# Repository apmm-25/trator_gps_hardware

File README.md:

# trator_gps_hardware
# This repository will hold the hardware for the tractor GPS connection board, leveraging an ESP32 microcontroller that will communicate with an ardusimple ZED F9P based board 
  - `board/` (has the ibom.html with the positions and instructions for soldering)
  - `docs/` (has the pdf datasheets of electronics components that were utilized)
  - `default_esp32_board/` (Kicad project with component zips, step model of the board, libraries and manufacture files )

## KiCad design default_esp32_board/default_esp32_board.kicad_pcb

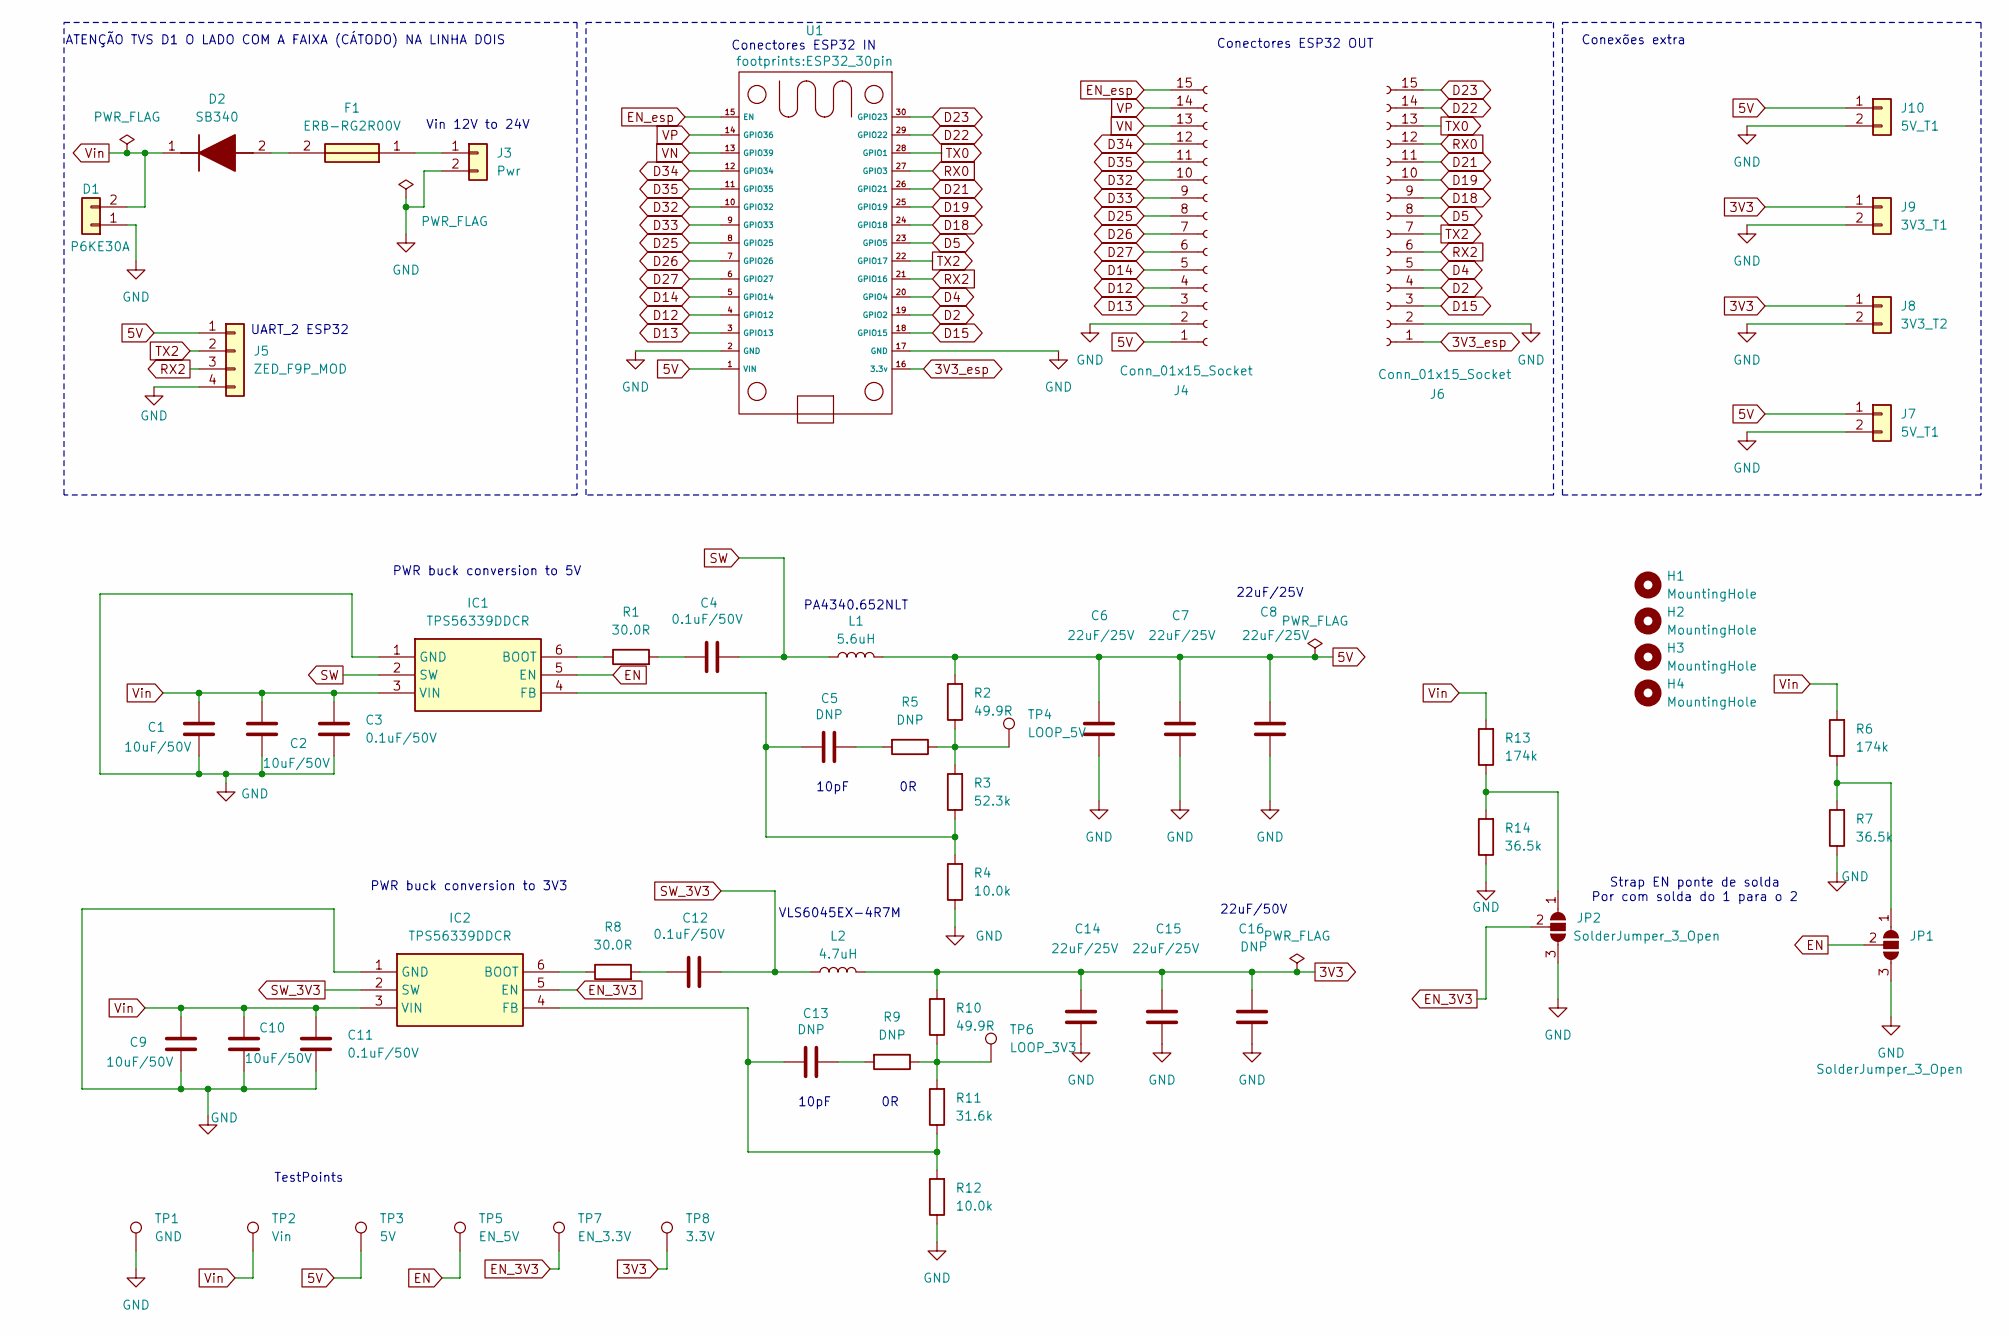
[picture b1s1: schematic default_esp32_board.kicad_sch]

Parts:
C1, C2, C9, C10: 10uF/50V; C_0805_2012Metric_Pad1.18x1.45mm_HandSolder
C3, C4, C11, C12: 0.1uF/50V; C_0805_2012Metric_Pad1.18x1.45mm_HandSolder
C5, C13, C16: DNP; C_0805_2012Metric_Pad1.18x1.45mm_HandSolder
C6, C7, C8, C14, C15: 22uF/25V; C_0805_2012Metric_Pad1.18x1.45mm_HandSolder
D1: P6KE30A; D_DO-15_P5.08mm_Vertical_KathodeUp
D2: SB340; Mouser Part Number 637-SB340
F1: ERB-RG2R00V; ERBRG4R00V; Mouser Part Number 667-ERB-RG2R00V
H1, H2, H3, H4: MountingHole; MountingHole_4.3mm_M4
IC1, IC2: TPS56339DDCR; Mouser Part Number 595-TPS56339DDCR
J3: Pwr; PinHeader_1x02_P2.54mm_Vertical
J4, J6: Conn_01x15_Socket; M20-7821546
J5: ZED_F9P_MOD; PinHeader_1x04_P2.54mm_Vertical
J7, J10: 5V_T1; PinHeader_1x02_P2.54mm_Vertical
J8: 3V3_T2; PinHeader_1x02_P2.54mm_Vertical
J9: 3V3_T1; PinHeader_1x02_P2.54mm_Vertical
JP1, JP2: SolderJumper_3_Open; SolderJumper-3_P1.3mm_Open_Pad1.0x1.5mm_NumberLabels
L1: 5.6uH; PA4340562NLT
L2: 4.7uH; VLS6045
R1, R8: 30.0R; R_0805_2012Metric_Pad1.20x1.40mm_HandSolder
R2, R10: 49.9R; R_0805_2012Metric_Pad1.20x1.40mm_HandSolder
R3: 52.3k; R_0805_2012Metric_Pad1.20x1.40mm_HandSolder
R4, R12: 10.0k; R_0805_2012Metric_Pad1.20x1.40mm_HandSolder
R5, R9: DNP; R_0805_2012Metric_Pad1.20x1.40mm_HandSolder
R6, R13: 174k; R_0805_2012Metric_Pad1.20x1.40mm_HandSolder
R7, R14: 36.5k; R_0805_2012Metric_Pad1.20x1.40mm_HandSolder
R11: 31.6k; R_0805_2012Metric_Pad1.20x1.40mm_HandSolder
TP1: GND; TestPoint_Plated_Hole_D2.0mm
TP2: Vin; TestPoint_Plated_Hole_D2.0mm
TP3: 5V; TestPoint_Plated_Hole_D2.0mm
TP4: LOOP_5V; TestPoint_Plated_Hole_D2.0mm
TP5: EN_5V; TestPoint_Plated_Hole_D2.0mm
TP6: LOOP_3V3; TestPoint_Plated_Hole_D2.0mm
TP7: EN_3.3V; TestPoint_Plated_Hole_D2.0mm
TP8: 3.3V; TestPoint_Plated_Hole_D2.0mm
U1: ESP32_30pin

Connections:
3V3: C14.1, C15.1, C16.1, J8.1, J9.1, L2.2, R10.2, TP8.1
3V3_esp: J6.1, U1.16 (3.3v)
5V: C6.1, C7.1, C8.1, J4.1, J5.1, J7.1, J10.1, L1.2, R2.2, TP3.1, U1.1 (VIN)
D2: J6.4, U1.19 (GPIO2)
D4: J6.5, U1.20 (GPIO4)
D5: J6.8, U1.23 (GPIO5)
D12: J4.4, U1.4 (GPIO12)
D13: J4.3, U1.3 (GPIO13)
D14: J4.5, U1.5 (GPIO14)
D15: J6.3, U1.18 (GPIO15)
D18: J6.9, U1.24 (GPIO18)
D19: J6.10, U1.25 (GPIO19)
D21: J6.11, U1.26 (GPIO21)
D22: J6.14, U1.29 (GPIO22)
D23: J6.15, U1.30 (GPIO23)
D25: J4.8, U1.8 (GPIO25)
D26: J4.7, U1.7 (GPIO26)
D27: J4.6, U1.6 (GPIO27)
D32: J4.10, U1.10 (GPIO32)
D33: J4.9, U1.9 (GPIO33)
D34: J4.12, U1.12 (GPIO34)
D35: J4.11, U1.11 (GPIO35)
EN: IC1.5 (EN), JP1.2 (C), TP5.1
EN_3V3: IC2.5 (EN), JP2.2 (C), TP7.1
EN_esp: J4.15, U1.15 (EN)
GND: C1.2, C2.2, C3.2, C6.2, C7.2, C8.2, C9.2, C10.2, C11.2, C14.2, C15.2, C16.2, D1.1, IC1.1 (GND), IC2.1 (GND), J3.2, J4.2, J5.4, J6.2, J7.2, J8.2, J9.2, J10.2, JP1.3 (B), JP2.3 (B), R4.1, R7.1, R12.1, R14.1, TP1.1, U1.2 (GND), U1.17 (GND)
unnamed: C4.1, R1.2
unnamed: C5.2, R5.2
unnamed: C12.1, R8.2
unnamed: C13.2, R9.2
unnamed: D2.2 (A), F1.2
unnamed: IC1.6 (BOOT), R1.1
unnamed: C5.1, IC1.4 (FB), R3.1, R4.2
unnamed: IC2.6 (BOOT), R8.1
unnamed: C13.1, IC2.4 (FB), R11.1, R12.2
unnamed: F1.1, J3.1
unnamed: JP1.1 (A), R6.1, R7.2
unnamed: JP2.1 (A), R13.1, R14.2
unnamed: R2.1, R3.2, R5.1, TP4.1
unnamed: R9.1, R10.1, R11.2, TP6.1
RX0: J6.12, U1.27 (GPIO3)
RX2: J5.3, J6.6, U1.21 (GPIO16)
SW: C4.2, IC1.2 (SW), L1.1
SW_3V3: C12.2, IC2.2 (SW), L2.1
TX0: J6.13, U1.28 (GPIO1)
TX2: J5.2, J6.7, U1.22 (GPIO17)
VN: J4.13, U1.13 (GPIO39)
VP: J4.14, U1.14 (GPIO36)
Vin: C1.1, C2.1, C3.1, C9.1, C10.1, C11.1, D1.2, D2.1 (K), IC1.3 (VIN), IC2.3 (VIN), R6.2, R13.2, TP2.1

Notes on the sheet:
Vin 12V to 24V
TestPoints
10pF
PA4340.652NLT
Strap EN ponte de solda Por com solda do 1 para o 2
PWR buck conversion to 5V
Conexões extra
PWR buck conversion to 3V3
Conectores ESP32 IN
22uF/50V
UART_2 ESP32
Conectores ESP32 OUT
VLS6045EX-4R7M
ATENÇÃO TVS D1 O LADO COM A FAIXA (CÁTODO) NA LINHA DOIS
22uF/25V

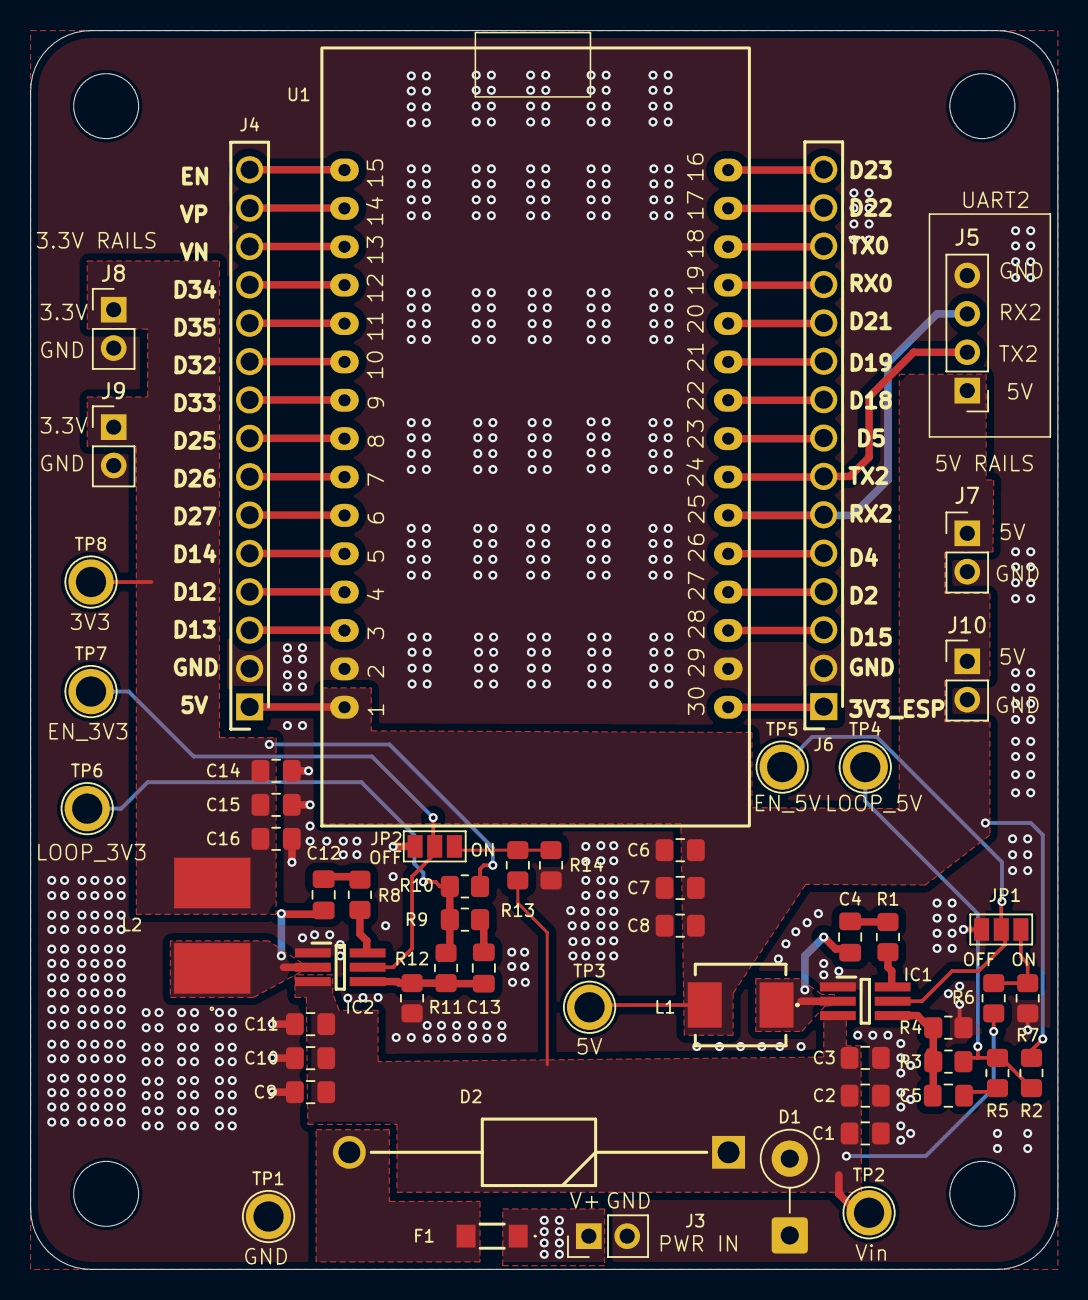
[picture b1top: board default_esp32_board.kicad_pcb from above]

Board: 2 copper layers, 68.0 x 82.0 mm, 60 parts (0 on the bottom side), 49 nets.

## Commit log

2026-06-18 Initial commit with all the current files on the KiCAD hardware development
2026-06-18 Update README with repository structure details
    Added additional details about the repository structure and contents.
2026-06-18 Format README.md for better readability
2026-06-19 Fixed esp32 30 pin footprint and changed the connections and silkscreen to match it
2026-06-19 Enhance README with communication details
    Updated project description to include communication details with ardusimple ZED F9P.
2026-06-22 Changed bad ESP32 30 pin footprint, changed bucks footprints to make it easier to solder in the new version
